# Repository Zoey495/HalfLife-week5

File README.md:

# HalfLife-week5
Making a small keyboard for an easier time watching/reading on the internet.
I used Kicad's schematic and PCB editors, as well as arduino ide for the code.

3D view

front

back

A schematic diagram is a diagram showing how all the parts and components need to be connected together. This is really handy when you start making the PCB.

Schematic

A PCB is a board where all the components are later soldered (connected) onto. It allows all the components to communicate and send signals to the brain (which in this case is the xiao).

PCB 

Using Arduino ide and a built in library called keyboard, I wrote the code so that when certain button is pressed, a certain "input key" to then sent to the computer.
Sneak peek of code (You can see the entire thing in Keyboard.ino)

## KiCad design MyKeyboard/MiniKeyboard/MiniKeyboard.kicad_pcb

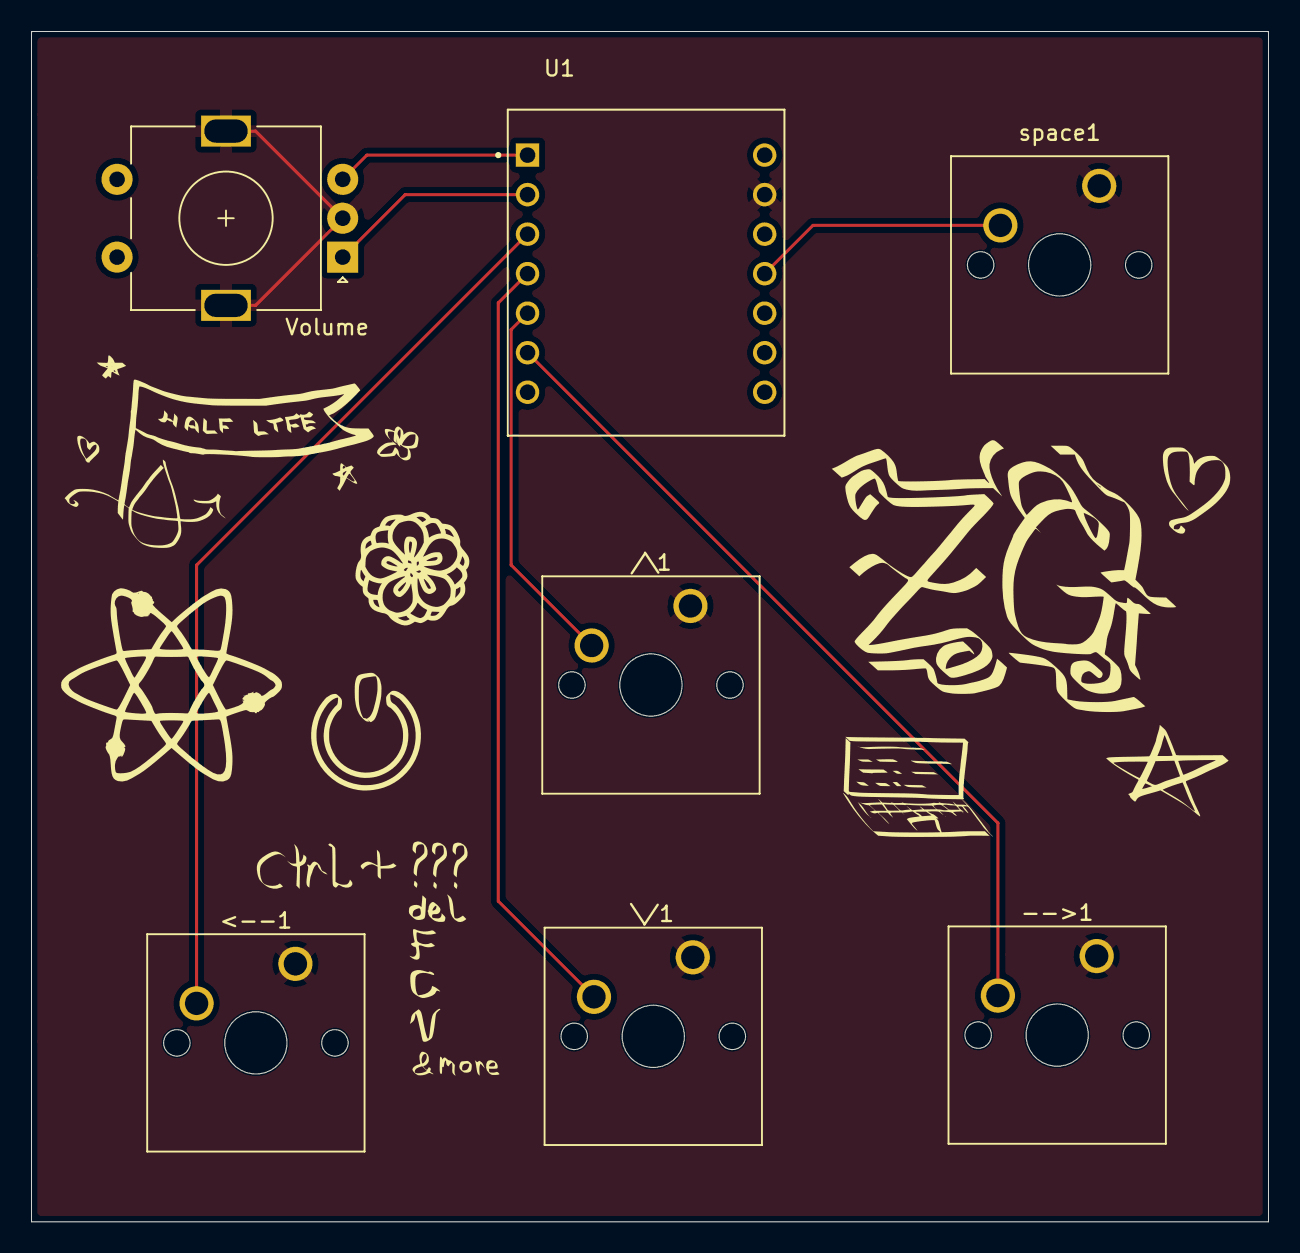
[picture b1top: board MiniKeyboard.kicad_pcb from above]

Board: 2 copper layers, 79.5 x 76.5 mm, 7 parts (0 on the bottom side), 8 nets.

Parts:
-->1: SW_Push; SW_Cherry_MX_1.00u_PCB
/\1: SW_Push; SW_Cherry_MX_1.00u_PCB
<--1: SW_Push; SW_Cherry_MX_1.00u_PCB
U1: XIAO-ESP32-S3; XIAO ESP32-S3
Volume: RotaryEncoder_Switch_MP; RotaryEncoder_Alps_EC11E-Switch_Vertical_H20mm
\/1: SW_Push; SW_Cherry_MX_1.00u_PCB
space1: SW_Push; SW_Cherry_MX_1.00u_PCB

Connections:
/Decrease: U1.1 (D0/GPIO1), Volume.B
/GND: -->1.1, /\1.1, <--1.1, U1.13 (GND), Volume.C, Volume.MP, \/1.1, space1.1
/Increase: U1.2 (D1/GPIO2), Volume.A
/SW_Down: U1.4 (D3/GPIO4), \/1.2
/SW_Left: <--1.2, U1.3 (D2/GPIO3)
/SW_Right: -->1.2, U1.6 (D5/GPIO6)
/SW_Space: U1.11 (D10/GPIO9), space1.2
/SW_UP: /\1.2, U1.5 (D4/GPIO5)
